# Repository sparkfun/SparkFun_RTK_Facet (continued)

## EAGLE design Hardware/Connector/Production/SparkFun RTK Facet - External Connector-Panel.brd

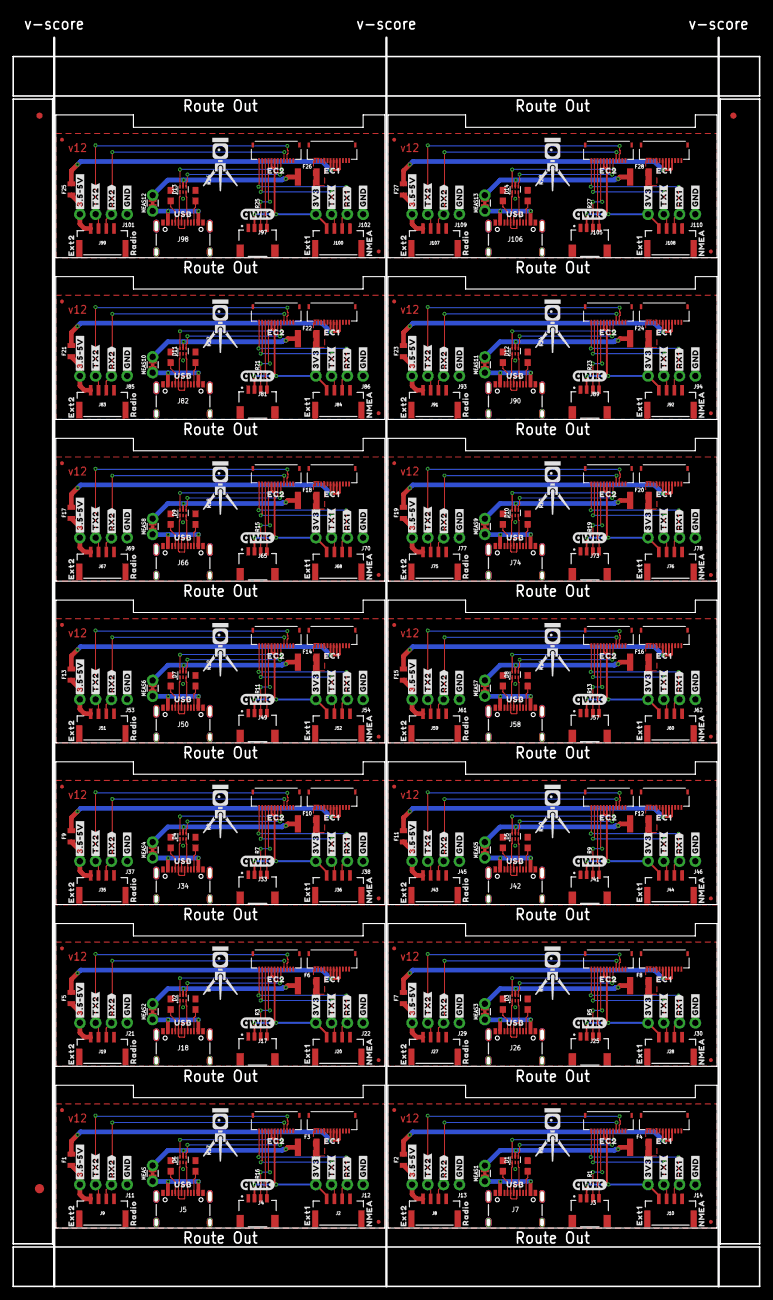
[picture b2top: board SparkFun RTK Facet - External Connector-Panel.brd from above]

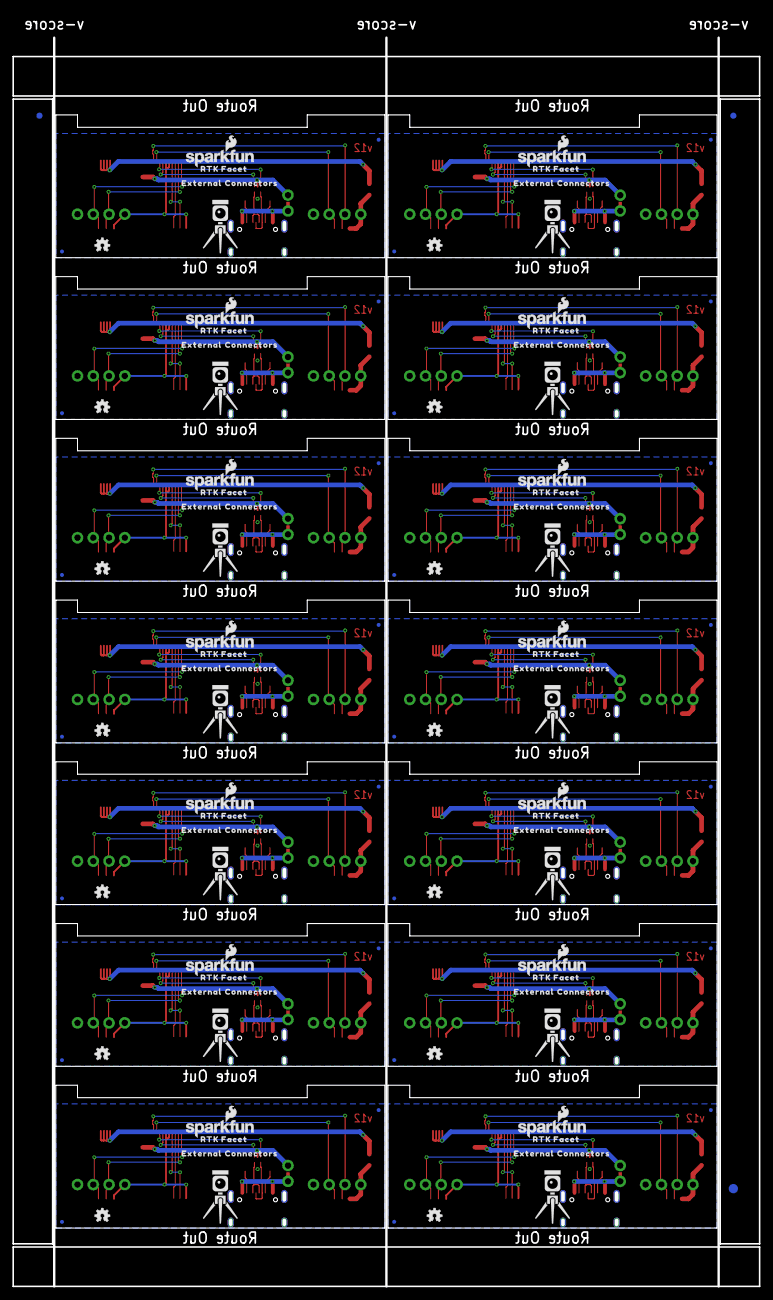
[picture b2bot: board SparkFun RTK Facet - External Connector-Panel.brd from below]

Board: 2 copper layers, 120.2 x 201.1 mm, 580 parts (115 on the bottom side), 266 nets.

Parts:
D1, D2, D3, D4, D5, D6, D7, D8, D9, D10, D11, D12, D13, D14: PRTR5V0U2F; SOT886
E$1, E$2, E$3, E$4: FIDUCIAL-1X2
E$5, E$6: FIDUCIAL-1.5X3
F1, F2, F5, F7, F9, F11, F13, F15, F17, F19, F21, F23, F25, F27: 6V 0.5A; 0805
F3, F4, F6, F8, F10, F12, F14, F16, F18, F20, F22, F24, F26, F28: 6V/2A; 1210
J1, J6, J15, J16, J23, J24, J31, J32, J39, J40, J47, J48, J55, J56, J63, J64, J71, J72, J79, J80, J87, J88, J95, J96, J103, J104, J111, J112: FPC_12_0.5MM_BACKFLIP; FPC_12_DOUBLESIDED_BACKFLIP
J2, J8, J9, J10, J19, J20, J27, J28, J35, J36, J43, J44, J51, J52, J59, J60, J67, J68, J75, J76, J83, J84, J91, J92, J99, J100, J107, J108: JST-4-SMD-1.25MM-LOCKING
J3, J4, J17, J25, J33, J41, J49, J57, J65, J73, J81, J89, J97, J105: Qwiic; JST04_1MM_RA
J5, J7, J18, J26, J34, J42, J50, J58, J66, J74, J82, J90, J98, J106: u-blox USB; USB-C-16P-2LAYER-PADS
J11, J12, J13, J14, J21, J22, J29, J30, J37, J38, J45, J46, J53, J54, J61, J62, J69, J70, J77, J78, J85, J86, J93, J94, J101, J102, J109, J110: 1X04_NO_SILK
JP1, JP2, JP3, JP4, JP5, JP6, JP7, JP8, JP9, JP10, JP11, JP12, JP13, JP14, JP15, JP16, JP17, JP18, JP19, JP20, JP21, JP22, JP23, JP24, JP25, JP26, JP27, JP28, JP29, JP30, JP31, JP32, JP33, JP34, JP35, JP36, JP37, JP38, JP39, JP40, JP41, JP42, JP43, JP44, JP45, JP46, JP47, JP48, JP49, JP50, JP51, JP52, JP53, JP61, JP71, JP81: FIDUCIALUFIDUCIAL; FIDUCIAL-MICRO
LOGO1, LOGO4, LOGO7, LOGO10, LOGO13, LOGO16, LOGO19, LOGO22, LOGO25, LOGO28, LOGO31, LOGO34, LOGO37, LOGO40: OSHW-LOGOMINI; OSHW-LOGO-MINI
LOGO2, LOGO5, LOGO8, LOGO11, LOGO14, LOGO17, LOGO20, LOGO23, LOGO26, LOGO29, LOGO32, LOGO35, LOGO38, LOGO41: SFE_LOGO_NAME_FLAME.1_INCH; SFE_LOGO_NAME_FLAME_.1
LOGO3, LOGO6, LOGO9, LOGO12, LOGO15, LOGO18, LOGO21, LOGO24, LOGO27, LOGO30, LOGO33, LOGO36, LOGO39, LOGO42: QWIIC_LOGO_CONNECTOR; QWIIC_5.5MM
MEAS, MEAS1, MEAS2, MEAS3, MEAS4, MEAS5, MEAS6, MEAS7, MEAS8, MEAS9, MEAS10, MEAS11, MEAS12, MEAS13: COMBO-JUMPER_2_NC_TRACE
R1, R2, R3, R4, R5, R6, R7, R8, R9, R10, R11, R12, R13, R14, R15, R16, R17, R18, R19, R20, R21, R22, R23, R24, R25, R26, R27, R28: 5.1k; 0603
U$1, U$27, U$50, U$72, U$93, U$113, U$133, U$153, U$173, U$193, U$213, U$233, U$253, U$273: USB0
U$2, U$22, U$46, U$67, U$89, U$109, U$129, U$149, U$169, U$189, U$209, U$229, U$249, U$269: CONNECTORS1
U$3, U$13, U$32, U$33, U$55, U$56, U$77, U$78, U$98, U$99, U$118, U$119, U$138, U$139, U$158, U$159, U$178, U$179, U$198, U$199, U$218, U$219, U$238, U$239, U$258, U$259, U$278, U$279: RTK5#SVG0
U$4, U$28, U$51, U$73, U$94, U$114, U$134, U$154, U$174, U$194, U$214, U$234, U$254, U$274: EXT10
U$5, U$18, U$42, U$62, U$85, U$105, U$125, U$145, U$165, U$185, U$205, U$225, U$245, U$265: #3V3#0
U$6, U$29, U$52, U$74, U$95, U$115, U$135, U$155, U$175, U$195, U$215, U$235, U$255, U$275: EXT22
U$7, U$30, U$53, U$75, U$96, U$116, U$136, U$156, U$176, U$196, U$216, U$236, U$256, U$276: NMEA1
U$8, U$25, U$48, U$70, U$91, U$111, U$131, U$151, U$171, U$191, U$211, U$231, U$251, U$271: EC10
U$9, U$24, U$47, U$69, U$90, U$110, U$130, U$150, U$170, U$190, U$210, U$230, U$250, U$270: EXTERNAL0
U$10, U$35, U$39, U$58, U$80, U$101, U$121, U$141, U$161, U$181, U$201, U$221, U$241, U$261: #RX2#2
U$11, U$26, U$49, U$71, U$92, U$112, U$132, U$152, U$172, U$192, U$212, U$232, U$252, U$272: EC21
U$12, U$31, U$54, U$76, U$97, U$117, U$137, U$157, U$177, U$197, U$217, U$237, U$257, U$277: RADIO3
U$14, U$34, U$57, U$79, U$100, U$120, U$140, U$160, U$180, U$200, U$220, U$240, U$260, U$280: RTK_FACET0
U$15, U$36, U$40, U$59, U$81, U$102, U$122, U$142, U$162, U$182, U$202, U$222, U$242, U$262: #TX2#1
U$16, U$21, U$37, U$38, U$45, U$60, U$66, U$82, U$83, U$88, U$103, U$108, U$123, U$128, U$143, U$148, U$163, U$168, U$183, U$188, U$203, U$208, U$223, U$228, U$243, U$248, U$263, U$268: #GND#0
U$17, U$23, U$41, U$61, U$84, U$104, U$124, U$144, U$164, U$184, U$204, U$224, U$244, U$264: #3#5#5V#0
U$19, U$43, U$63, U$65, U$86, U$106, U$126, U$146, U$166, U$186, U$206, U$226, U$246, U$266: #TX1#1
U$20, U$44, U$64, U$68, U$87, U$107, U$127, U$147, U$167, U$187, U$207, U$227, U$247, U$267: #RX1#2

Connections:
3.3V: J2.1, J4.2, J6.7, J6.8, J12.4
3.3V1: J3.2, J10.1, J14.4, J16.7, J16.8
3.3V2: J17.2, J20.1, J22.4, J24.7, J24.8
3.3V3: J25.2, J28.1, J30.4, J32.7, J32.8
3.3V4: J33.2, J36.1, J38.4, J40.7, J40.8
3.3V5: J41.2, J44.1, J46.4, J48.7, J48.8
3.3V6: J49.2, J52.1, J54.4, J56.7, J56.8
3.3V7: J57.2, J60.1, J62.4, J64.7, J64.8
3.3V8: J65.2, J68.1, J70.4, J72.7, J72.8
3.3V9: J73.2, J76.1, J78.4, J80.7, J80.8
3.3V10: J81.2, J84.1, J86.4, J88.7, J88.8
3.3V11: J89.2, J92.1, J94.4, J96.7, J96.8
3.3V12: J97.2, J100.1, J102.4, J104.7, J104.8
3.3V13: J105.2, J108.1, J110.4, J112.7, J112.8
CC1: J5.A5, R17.2
CC2: J5.B5, R16.2
CC3: J7.A5, R2.2
CC4: J7.B5, R1.2
CC5: J18.A5, R4.2
CC6: J18.B5, R3.2
CC7: J26.A5, R6.2
CC8: J26.B5, R5.2
CC9: J34.A5, R8.2
CC10: J34.B5, R7.2
CC11: J42.A5, R10.2
CC12: J42.B5, R9.2
CC13: J50.A5, R12.2
CC14: J50.B5, R11.2
CC15: J58.A5, R14.2
CC16: J58.B5, R13.2
CC17: J66.A5, R18.2
CC18: J66.B5, R15.2
CC19: J74.A5, R20.2
CC20: J74.B5, R19.2
CC21: J82.A5, R22.2
CC22: J82.B5, R21.2
CC23: J90.A5, R24.2
CC24: J90.B5, R23.2
CC25: J98.A5, R26.2
CC26: J98.B5, R25.2
CC27: J106.A5, R28.2
CC28: J106.B5, R27.2
ESP_21/SDA: J4.3, J6.9
ESP_21/SDA1: J3.3, J16.9
ESP_21/SDA2: J17.3, J24.9
ESP_21/SDA3: J25.3, J32.9
ESP_21/SDA4: J33.3, J40.9
ESP_21/SDA5: J41.3, J48.9
ESP_21/SDA6: J49.3, J56.9
ESP_21/SDA7: J57.3, J64.9
ESP_21/SDA8: J65.3, J72.9
ESP_21/SDA9: J73.3, J80.9
ESP_21/SDA10: J81.3, J88.9
ESP_21/SDA11: J89.3, J96.9
ESP_21/SDA12: J97.3, J104.9
ESP_21/SDA13: J105.3, J112.9
ESP_22/SCL: J4.4, J6.10
ESP_22/SCL1: J3.4, J16.10
ESP_22/SCL2: J17.4, J24.10
ESP_22/SCL3: J25.4, J32.10
ESP_22/SCL4: J33.4, J40.10
ESP_22/SCL5: J41.4, J48.10
ESP_22/SCL6: J49.4, J56.10
ESP_22/SCL7: J57.4, J64.10
ESP_22/SCL8: J65.4, J72.10
ESP_22/SCL9: J73.4, J80.10
ESP_22/SCL10: J81.4, J88.10
ESP_22/SCL11: J89.4, J96.10
ESP_22/SCL12: J97.4, J104.10
ESP_22/SCL13: J105.4, J112.10
EXTERNAL_SERIAL1_RXI: J2.3, J6.12, J12.2
EXTERNAL_SERIAL1_RXI1: J10.3, J14.2, J16.12
EXTERNAL_SERIAL1_RXI2: J20.3, J22.2, J24.12
EXTERNAL_SERIAL1_RXI3: J28.3, J30.2, J32.12
EXTERNAL_SERIAL1_RXI4: J36.3, J38.2, J40.12
EXTERNAL_SERIAL1_RXI5: J44.3, J46.2, J48.12
EXTERNAL_SERIAL1_RXI6: J52.3, J54.2, J56.12
EXTERNAL_SERIAL1_RXI7: J60.3, J62.2, J64.12
EXTERNAL_SERIAL1_RXI8: J68.3, J70.2, J72.12
EXTERNAL_SERIAL1_RXI9: J76.3, J78.2, J80.12
EXTERNAL_SERIAL1_RXI10: J84.3, J86.2, J88.12
EXTERNAL_SERIAL1_RXI11: J92.3, J94.2, J96.12
EXTERNAL_SERIAL1_RXI12: J100.3, J102.2, J104.12
EXTERNAL_SERIAL1_RXI13: J108.3, J110.2, J112.12
EXTERNAL_SERIAL1_TXO: J2.2, J6.11, J12.3
EXTERNAL_SERIAL1_TXO1: J10.2, J14.3, J16.11
EXTERNAL_SERIAL1_TXO2: J20.2, J22.3, J24.11
EXTERNAL_SERIAL1_TXO3: J28.2, J30.3, J32.11
EXTERNAL_SERIAL1_TXO4: J36.2, J38.3, J40.11
EXTERNAL_SERIAL1_TXO5: J44.2, J46.3, J48.11
EXTERNAL_SERIAL1_TXO6: J52.2, J54.3, J56.11
EXTERNAL_SERIAL1_TXO7: J60.2, J62.3, J64.11
EXTERNAL_SERIAL1_TXO8: J68.2, J70.3, J72.11
EXTERNAL_SERIAL1_TXO9: J76.2, J78.3, J80.11
EXTERNAL_SERIAL1_TXO10: J84.2, J86.3, J88.11
EXTERNAL_SERIAL1_TXO11: J92.2, J94.3, J96.11
EXTERNAL_SERIAL1_TXO12: J100.2, J102.3, J104.11
EXTERNAL_SERIAL1_TXO13: J108.2, J110.3, J112.11
GND: D6.2, J1.1, J1.2, J1.3, J2.4, J4.1, J5.GND, J5.GND2, J5.SHLD1, J5.SHLD2, J5.SHLD3, J5.SHLD4, J6.1, J6.2, J9.4, J11.1, J12.1, R16.1, R17.1
GND1: D1.2, J3.1, J7.GND, J7.GND2, J7.SHLD1, J7.SHLD2, J7.SHLD3, J7.SHLD4, J8.4, J10.4, J13.1, J14.1, J15.1, J15.2, J15.3, J16.1, J16.2, R1.1, R2.1
GND2: D2.2, J17.1, J18.GND, J18.GND2, J18.SHLD1, J18.SHLD2, J18.SHLD3, J18.SHLD4, J19.4, J20.4, J21.1, J22.1, J23.1, J23.2, J23.3, J24.1, J24.2, R3.1, R4.1
GND3: D3.2, J25.1, J26.GND, J26.GND2, J26.SHLD1, J26.SHLD2, J26.SHLD3, J26.SHLD4, J27.4, J28.4, J29.1, J30.1, J31.1, J31.2, J31.3, J32.1, J32.2, R5.1, R6.1
GND4: D4.2, J33.1, J34.GND, J34.GND2, J34.SHLD1, J34.SHLD2, J34.SHLD3, J34.SHLD4, J35.4, J36.4, J37.1, J38.1, J39.1, J39.2, J39.3, J40.1, J40.2, R7.1, R8.1
GND5: D5.2, J41.1, J42.GND, J42.GND2, J42.SHLD1, J42.SHLD2, J42.SHLD3, J42.SHLD4, J43.4, J44.4, J45.1, J46.1, J47.1, J47.2, J47.3, J48.1, J48.2, R9.1, R10.1
GND6: D7.2, J49.1, J50.GND, J50.GND2, J50.SHLD1, J50.SHLD2, J50.SHLD3, J50.SHLD4, J51.4, J52.4, J53.1, J54.1, J55.1, J55.2, J55.3, J56.1, J56.2, R11.1, R12.1
GND7: D8.2, J57.1, J58.GND, J58.GND2, J58.SHLD1, J58.SHLD2, J58.SHLD3, J58.SHLD4, J59.4, J60.4, J61.1, J62.1, J63.1, J63.2, J63.3, J64.1, J64.2, R13.1, R14.1
GND8: D9.2, J65.1, J66.GND, J66.GND2, J66.SHLD1, J66.SHLD2, J66.SHLD3, J66.SHLD4, J67.4, J68.4, J69.1, J70.1, J71.1, J71.2, J71.3, J72.1, J72.2, R15.1, R18.1
GND9: D10.2, J73.1, J74.GND, J74.GND2, J74.SHLD1, J74.SHLD2, J74.SHLD3, J74.SHLD4, J75.4, J76.4, J77.1, J78.1, J79.1, J79.2, J79.3, J80.1, J80.2, R19.1, R20.1
GND10: D11.2, J81.1, J82.GND, J82.GND2, J82.SHLD1, J82.SHLD2, J82.SHLD3, J82.SHLD4, J83.4, J84.4, J85.1, J86.1, J87.1, J87.2, J87.3, J88.1, J88.2, R21.1, R22.1
GND11: D12.2, J89.1, J90.GND, J90.GND2, J90.SHLD1, J90.SHLD2, J90.SHLD3, J90.SHLD4, J91.4, J92.4, J93.1, J94.1, J95.1, J95.2, J95.3, J96.1, J96.2, R23.1, R24.1
GND12: D13.2, J97.1, J98.GND, J98.GND2, J98.SHLD1, J98.SHLD2, J98.SHLD3, J98.SHLD4, J99.4, J100.4, J101.1, J102.1, J103.1, J103.2, J103.3, J104.1, J104.2, R25.1, R26.1
GND13: D14.2, J105.1, J106.GND, J106.GND2, J106.SHLD1, J106.SHLD2, J106.SHLD3, J106.SHLD4, J107.4, J108.4, J109.1, J110.1, J111.1, J111.2, J111.3, J112.1, J112.2, R27.1, R28.1
unnamed: F2.1, J8.1, J13.4
unnamed: F5.1, J19.1, J21.4
unnamed: F1.1, J9.1, J11.4
unnamed: F7.1, J27.1, J29.4
unnamed: F9.1, J35.1, J37.4
unnamed: F11.1, J43.1, J45.4
unnamed: F13.1, J51.1, J53.4
unnamed: F15.1, J59.1, J61.4
unnamed: F17.1, J67.1, J69.4
unnamed: F19.1, J75.1, J77.4
unnamed: F21.1, J83.1, J85.4
unnamed: F23.1, J91.1, J93.4
unnamed: F25.1, J99.1, J101.4
unnamed: F27.1, J107.1, J109.4
USB1_D_M: D6.1, J5.A7, J5.B7
USB1_D_M1: D1.1, J7.A7, J7.B7
USB1_D_M2: D2.1, J18.A7, J18.B7
USB1_D_M3: D3.1, J26.A7, J26.B7
USB1_D_M4: D4.1, J34.A7, J34.B7
USB1_D_M5: D5.1, J42.A7, J42.B7
USB1_D_M6: D7.1, J50.A7, J50.B7
USB1_D_M7: D8.1, J58.A7, J58.B7
USB1_D_M8: D9.1, J66.A7, J66.B7
USB1_D_M9: D10.1, J74.A7, J74.B7
USB1_D_M10: D11.1, J82.A7, J82.B7
USB1_D_M11: D12.1, J90.A7, J90.B7
USB1_D_M12: D13.1, J98.A7, J98.B7
USB1_D_M13: D14.1, J106.A7, J106.B7
USB1_D_P: D6.3, J5.A6, J5.B6
USB1_D_P1: D1.3, J7.A6, J7.B6
USB1_D_P2: D2.3, J18.A6, J18.B6
USB1_D_P3: D3.3, J26.A6, J26.B6
USB1_D_P4: D4.3, J34.A6, J34.B6
USB1_D_P5: D5.3, J42.A6, J42.B6
USB1_D_P6: D7.3, J50.A6, J50.B6
USB1_D_P7: D8.3, J58.A6, J58.B6
USB1_D_P8: D9.3, J66.A6, J66.B6
USB1_D_P9: D10.3, J74.A6, J74.B6
USB1_D_P10: D11.3, J82.A6, J82.B6
USB1_D_P11: D12.3, J90.A6, J90.B6
USB1_D_P12: D13.3, J98.A6, J98.B6
USB1_D_P13: D14.3, J106.A6, J106.B6
USB_DM: D6.6, J6.5
USB_DM1: D1.6, J16.5
USB_DM2: D2.6, J24.5
USB_DM3: D3.6, J32.5
USB_DM4: D4.6, J40.5
USB_DM5: D5.6, J48.5
USB_DM6: D7.6, J56.5
USB_DM7: D8.6, J64.5
USB_DM8: D9.6, J72.5
USB_DM9: D10.6, J80.5
USB_DM10: D11.6, J88.5
USB_DM11: D12.6, J96.5
USB_DM12: D13.6, J104.5
USB_DM13: D14.6, J112.5
USB_DP: D6.4, J6.6
USB_DP1: D1.4, J16.6
USB_DP2: D2.4, J24.6
USB_DP3: D3.4, J32.6
USB_DP4: D4.4, J40.6
USB_DP5: D5.4, J48.6
USB_DP6: D7.4, J56.6
USB_DP7: D8.4, J64.6
USB_DP8: D9.4, J72.6
USB_DP9: D10.4, J80.6
USB_DP10: D11.4, J88.6
USB_DP11: D12.4, J96.6
USB_DP12: D13.4, J104.6
USB_DP13: D14.4, J112.6
VIN: J5.VBUS1, J5.VBUS2, MEAS.1, MEAS.3
VIN1: D6.5, F3.1, MEAS.2, MEAS.4
VIN2: J7.VBUS1, J7.VBUS2, MEAS1.1, MEAS1.3
VIN3: D1.5, F4.1, MEAS1.2, MEAS1.4
VIN4: J18.VBUS1, J18.VBUS2, MEAS2.1, MEAS2.3
VIN5: D2.5, F6.1, MEAS2.2, MEAS2.4
VIN6: J26.VBUS1, J26.VBUS2, MEAS3.1, MEAS3.3
VIN7: D3.5, F8.1, MEAS3.2, MEAS3.4
VIN8: J34.VBUS1, J34.VBUS2, MEAS4.1, MEAS4.3
VIN9: D4.5, F10.1, MEAS4.2, MEAS4.4
VIN10: J42.VBUS1, J42.VBUS2, MEAS5.1, MEAS5.3
VIN11: D5.5, F12.1, MEAS5.2, MEAS5.4
VIN12: J50.VBUS1, J50.VBUS2, MEAS6.1, MEAS6.3
VIN13: D7.5, F14.1, MEAS6.2, MEAS6.4
VIN14: J58.VBUS1, J58.VBUS2, MEAS7.1, MEAS7.3
VIN15: D8.5, F16.1, MEAS7.2, MEAS7.4
VIN16: J66.VBUS1, J66.VBUS2, MEAS8.1, MEAS8.3
VIN17: D9.5, F18.1, MEAS8.2, MEAS8.4
VIN18: J74.VBUS1, J74.VBUS2, MEAS9.1, MEAS9.3
VIN19: D10.5, F20.1, MEAS9.2, MEAS9.4
VIN20: J82.VBUS1, J82.VBUS2, MEAS10.1, MEAS10.3
VIN21: D11.5, F22.1, MEAS10.2, MEAS10.4
VIN22: J90.VBUS1, J90.VBUS2, MEAS11.1, MEAS11.3
VIN23: D12.5, F24.1, MEAS11.2, MEAS11.4
VIN24: J98.VBUS1, J98.VBUS2, MEAS12.1, MEAS12.3
VIN25: D13.5, F26.1, MEAS12.2, MEAS12.4
VIN26: J106.VBUS1, J106.VBUS2, MEAS13.1, MEAS13.3
VIN27: D14.5, F28.1, MEAS13.2, MEAS13.4
V_BATT: F1.2, J1.4, J1.5, J1.6, J1.7
V_BATT1: F2.2, J15.4, J15.5, J15.6, J15.7
V_BATT2: F5.2, J23.4, J23.5, J23.6, J23.7
V_BATT3: F7.2, J31.4, J31.5, J31.6, J31.7
V_BATT4: F9.2, J39.4, J39.5, J39.6, J39.7
V_BATT5: F11.2, J47.4, J47.5, J47.6, J47.7
V_BATT6: F13.2, J55.4, J55.5, J55.6, J55.7
V_BATT7: F15.2, J63.4, J63.5, J63.6, J63.7
V_BATT8: F17.2, J71.4, J71.5, J71.6, J71.7
V_BATT9: F19.2, J79.4, J79.5, J79.6, J79.7
V_BATT10: F21.2, J87.4, J87.5, J87.6, J87.7
V_BATT11: F23.2, J95.4, J95.5, J95.6, J95.7
V_BATT12: F25.2, J103.4, J103.5, J103.6, J103.7
V_BATT13: F27.2, J111.4, J111.5, J111.6, J111.7
V_USB: F3.2, J1.9, J1.10, J1.11, J1.12
V_USB1: F4.2, J15.9, J15.10, J15.11, J15.12
V_USB2: F6.2, J23.9, J23.10, J23.11, J23.12
V_USB3: F8.2, J31.9, J31.10, J31.11, J31.12
V_USB4: F10.2, J39.9, J39.10, J39.11, J39.12
V_USB5: F12.2, J47.9, J47.10, J47.11, J47.12
V_USB6: F14.2, J55.9, J55.10, J55.11, J55.12
V_USB7: F16.2, J63.9, J63.10, J63.11, J63.12
V_USB8: F18.2, J71.9, J71.10, J71.11, J71.12
V_USB9: F20.2, J79.9, J79.10, J79.11, J79.12
V_USB10: F22.2, J87.9, J87.10, J87.11, J87.12
V_USB11: F24.2, J95.9, J95.10, J95.11, J95.12
V_USB12: F26.2, J103.9, J103.10, J103.11, J103.12
V_USB13: F28.2, J111.9, J111.10, J111.11, J111.12
ZED-RXI1: J8.3, J13.2, J16.4
ZED-RXI2: J6.4, J9.3, J11.2
ZED-RXI3: J19.3, J21.2, J24.4
ZED-RXI4: J27.3, J29.2, J32.4
ZED-RXI5: J35.3, J37.2, J40.4
ZED-RXI6: J43.3, J45.2, J48.4
ZED-RXI7: J51.3, J53.2, J56.4
ZED-RXI8: J59.3, J61.2, J64.4
ZED-RXI9: J67.3, J69.2, J72.4
ZED-RXI10: J75.3, J77.2, J80.4
ZED-RXI11: J83.3, J85.2, J88.4
ZED-RXI12: J91.3, J93.2, J96.4
ZED-RXI13: J99.3, J101.2, J104.4
ZED-RXI14: J107.3, J109.2, J112.4
ZED-TXO1: J8.2, J13.3, J16.3
ZED-TXO2: J6.3, J9.2, J11.3
ZED-TXO3: J19.2, J21.3, J24.3
ZED-TXO4: J27.2, J29.3, J32.3
ZED-TXO5: J35.2, J37.3, J40.3
ZED-TXO6: J43.2, J45.3, J48.3
ZED-TXO7: J51.2, J53.3, J56.3
ZED-TXO8: J59.2, J61.3, J64.3
ZED-TXO9: J67.2, J69.3, J72.3
ZED-TXO10: J75.2, J77.3, J80.3
ZED-TXO11: J83.2, J85.3, J88.3
ZED-TXO12: J91.2, J93.3, J96.3
ZED-TXO13: J99.2, J101.3, J104.3
ZED-TXO14: J107.2, J109.3, J112.3
